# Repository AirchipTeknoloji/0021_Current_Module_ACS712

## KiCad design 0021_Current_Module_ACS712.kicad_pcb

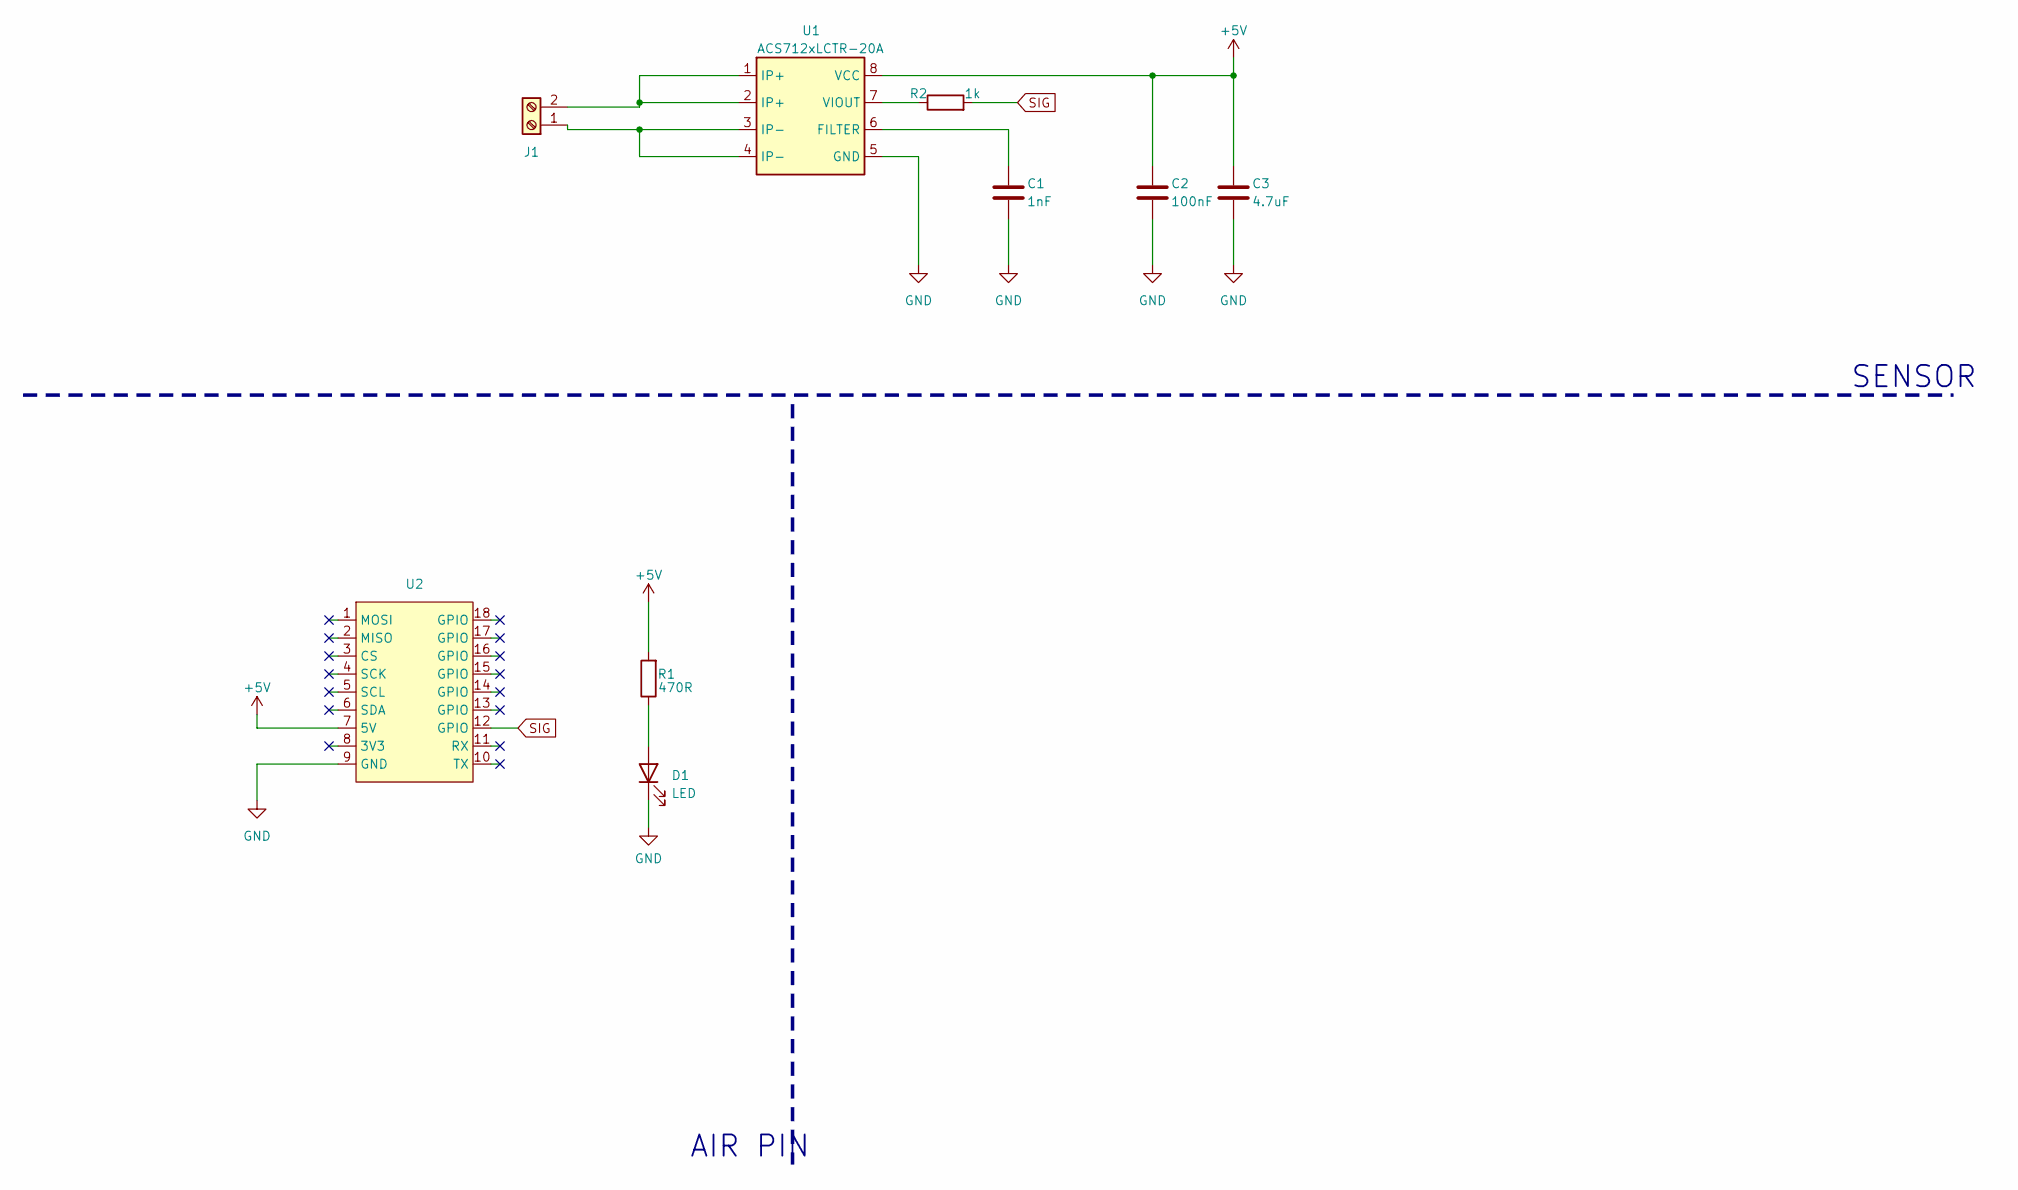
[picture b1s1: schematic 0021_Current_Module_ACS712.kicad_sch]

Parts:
C1: 1nF; C_0805_2012Metric
C2: 100nF; C_0805_2012Metric
C3: 4.7uF; C_0805_2012Metric
D1: LED; LED_0805_2012Metric
J1: Screw_Terminal_01x02; barriyer_7.62
R1: 470R; R_0805_2012Metric
R2: 1k; R_0805_2012Metric
U1: ACS712xLCTR-20A; SOIC-8_3.9x4.9mm_P1.27mm
U2: air_module

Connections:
+5V: C2.1, C3.1, R1.2, U1.8 (VCC), U2.7 (5V)
GND: C1.2, C2.2, C3.2, D1.1 (K), U1.5 (GND), U2.9 (GND)
unnamed: D1.2 (A), R1.1
unnamed: J1.1, U1.3 (IP-), U1.4 (IP-)
unnamed: J1.2, U1.1 (IP+), U1.2 (IP+)
unnamed: C1.1, U1.6 (FILTER)
unnamed: R2.1, U1.7 (VIOUT)
SIG: R2.2, U2.12 (GPIO)

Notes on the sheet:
SENSOR
AIR PIN

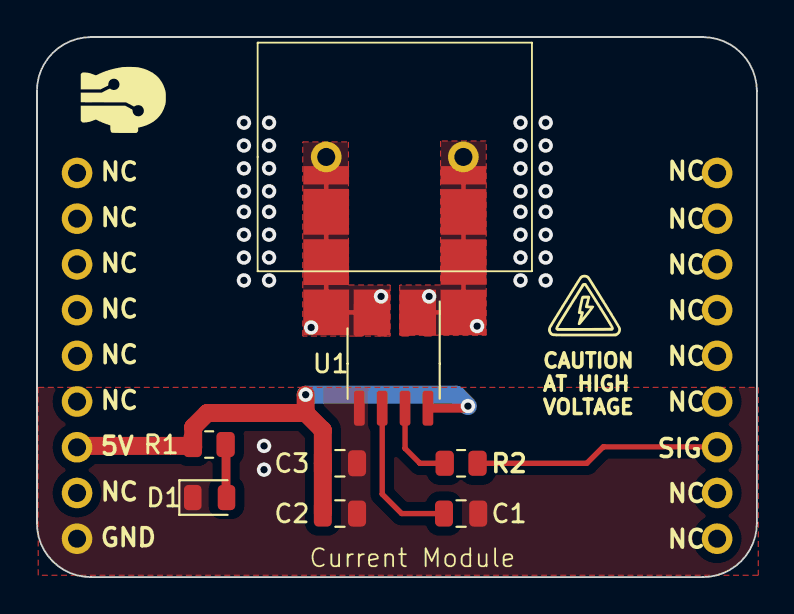
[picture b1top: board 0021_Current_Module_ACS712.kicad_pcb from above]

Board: 2 copper layers, 40.0 x 30.0 mm, 9 parts (0 on the bottom side), 8 nets.
